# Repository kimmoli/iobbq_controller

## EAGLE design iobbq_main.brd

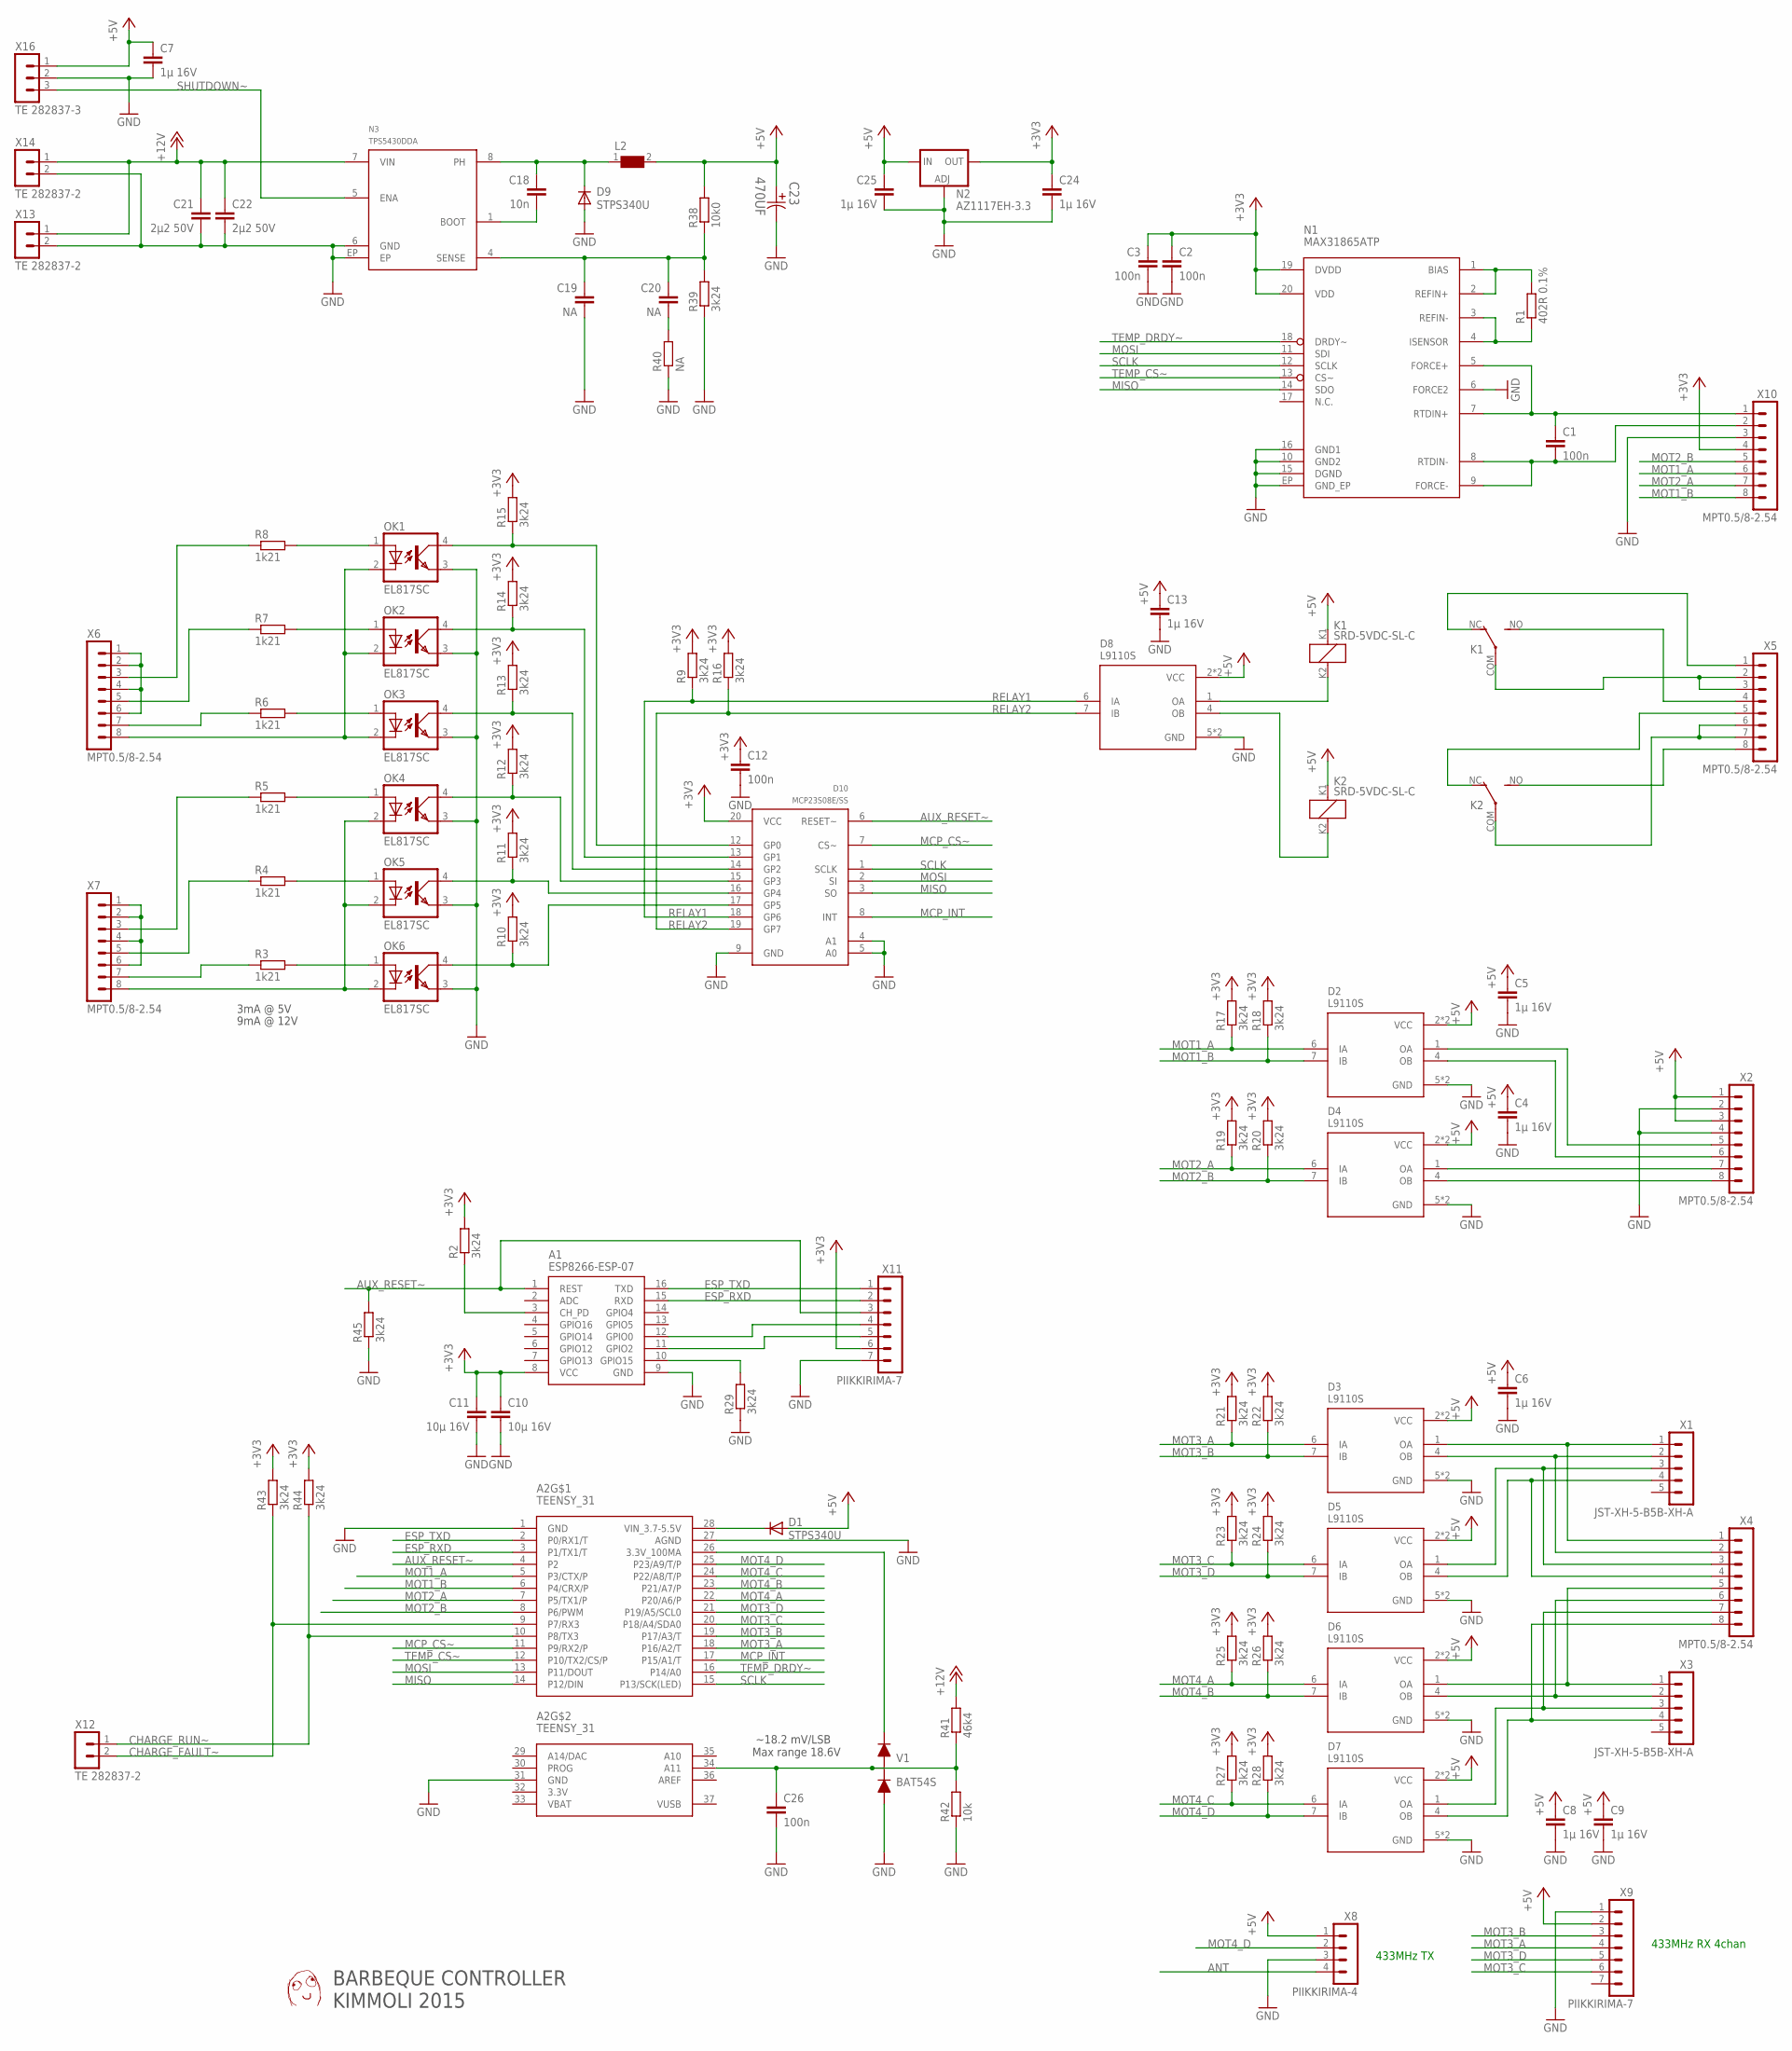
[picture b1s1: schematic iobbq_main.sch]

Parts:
A1: ESP8266-ESP-07
A2: TEENSY_31; TEENSY_31_THONLY
C1, C2, C3, C12, C26: 100n; C0603
C4, C5, C6, C7, C8, C9, C13, C24, C25: 1µ 16V; C0805
C10, C11: 10µ 16V; C0805
C18: 10n; C0805
C19, C20: NA; C0603
C21, C22: 2µ2 50V; C0805
C23: 470UF; CAPAE1350X1400N
D1, D9: STPS340U; SMB
D2, D3, D4, D5, D6, D7, D8: L9110S; SOIC8-N_MC
D10: MCP23S08E/SS; SSOP-20
K1, K2: SRD-5VDC-SL-C; SRD-SL-C
L2: WE-PD-7447709220_1260/1245/1280/1210; WE-PD_1260/1245/1280/1210
N1: MAX31865ATP; TQFN-20
N2: AZ1117EH-3.3; SOT223
N3: TPS5430DDA; SOIC8-N-EP
OK1, OK2, OK3, OK4, OK5, OK6: EL817SC; SMD4-7
R1: 402R 0.1%; R0603
R2, R9, R10, R11, R12, R13, R14, R15, R16, R17, R18, R19, R20, R21, R22, R23, R24, R25, R26, R27, R28, R29, R39, R43, R44, R45: 3k24; R0603
R3, R4, R5, R6, R7, R8: 1k21; R0805
R38: 10k0; R0603
R40: NA; R0603
R41: 46k4; R0603
R42: 10k; R0603
U$3: DAFUG
V1: BAT54S; SOT23
X1, X3: JST-XH-5-B5B-XH-A; JST-XH-5
X2, X4, X5, X6, X7, X10: MPT0.5/8-2.54
X8: PIIKKIRIMA-4
X9, X11: PIIKKIRIMA-7
X12, X13, X14: TE 282837-2; TE_RUUVILIITIN2
X16: TE 282837-3; TE_RUUVILIITIN3

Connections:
+3V3: A1.8 (VCC), C2.1, C3.1, C10.1, C11.1, C12.1, C24.1, D10.20 (VCC), N1.19 (DVDD), N1.20 (VDD), N2.4 (OUT), R2.2, R9.2, R10.2, R11.2, R12.2, R13.2, R14.2, R15.2, R16.2, R17.2, R18.2, R19.2, R20.2, R21.2, R22.2, R23.2, R24.2, R25.2, R26.2, R27.2, R28.2, R43.2, R44.2, X10.4, X11.6
+5V: C4.1, C5.1, C6.1, C7.1, C8.1, C9.1, C13.1, C23.1, C25.1, D1.A, D2.2 (VCC), D2.3 (VCC), D3.2 (VCC), D3.3 (VCC), D4.2 (VCC), D4.3 (VCC), D5.2 (VCC), D5.3 (VCC), D6.2 (VCC), D6.3 (VCC), D7.2 (VCC), D7.3 (VCC), D8.2 (VCC), D8.3 (VCC), K1.K1 (1), K2.K1 (1), L2.2, N2.3 (IN), R38.2, X2.1, X2.3, X8.1, X9.2, X16.1
+12V: C21.1, C22.1, N3.7 (VIN), R41.2, X13.1, X14.1
ANT: X8.4
AUX_RESET~: A1.1 (REST), A2.4 (P2), D10.6 (RESET~), R45.2, X11.3
CHARGE_FAULT~: A2.9 (P7/RX3), R43.1, X12.2
CHARGE_RUN~: A2.10 (P8/TX3), R44.1, X12.1
ESP_RXD: A1.15 (RXD), A2.3 (P1/TX1/T), X11.2
ESP_TXD: A1.16 (TXD), A2.2 (P0/RX1/T), X11.1
GND: A1.9 (GND), A2.1 (GND), A2.27 (AGND), A2.31 (GND), C2.2, C3.2, C4.2, C5.2, C6.2, C7.2, C8.2, C9.2, C10.2, C11.2, C12.2, C13.2, C19.2, C21.2, C22.2, C23.2, C24.2, C25.2, C26.2, D2.5 (GND), D2.8 (GND), D3.5 (GND), D3.8 (GND), D4.5 (GND), D4.8 (GND), D5.5 (GND), D5.8 (GND), D6.5 (GND), D6.8 (GND), D7.5 (GND), D7.8 (GND), D8.5 (GND), D8.8 (GND), D9.A, D10.4 (A1), D10.5 (A0), D10.9 (GND), N1.6 (FORCE2), N1.10 (GND2), N1.15 (DGND), N1.16 (GND1), N1.EP (GND_EP), N2.1 (ADJ), N3.6 (GND), N3.EP, OK1.3 (EMIT), OK2.3 (EMIT), OK3.3 (EMIT), OK4.3 (EMIT), OK5.3 (EMIT), OK6.3 (EMIT), R29.1, R39.1, R40.1, R42.1, R45.1, V1.1, X2.2, X2.4, X8.3, X9.1, X10.3, X11.7, X13.2, X14.2, X16.2
MCP_CS~: A2.11 (P9/RX2/P), D10.7 (CS~)
MCP_INT: A2.17 (P15/A1/T), D10.8 (INT)
MISO: A2.14 (P12/DIN), D10.3 (SO), N1.14 (SDO)
MOSI: A2.13 (P11/DOUT), D10.2 (SI), N1.11 (SDI)
MOT1_A: A2.5 (P3/CTX/P), D2.6 (IA), R17.1, X10.6
MOT1_B: A2.6 (P4/CRX/P), D2.7 (IB), R18.1, X10.8
MOT2_A: A2.7 (P5/TX1/P), D4.6 (IA), R19.1, X10.7
MOT2_B: A2.8 (P6/PWM), D4.7 (IB), R20.1, X10.5
MOT3_A: A2.18 (P16/A2/T), D3.6 (IA), R21.1, X9.4
MOT3_B: A2.19 (P17/A3/T), D3.7 (IB), R22.1, X9.3
MOT3_C: A2.20 (P18/A4/SDA0), D5.6 (IA), R23.1, X9.6
MOT3_D: A2.21 (P19/A5/SCL0), D5.7 (IB), R24.1, X9.5
MOT4_A: A2.22 (P20/A6/P), D6.6 (IA), R25.1
MOT4_B: A2.23 (P21/A7/P), D6.7 (IB), R26.1
MOT4_C: A2.24 (P22/A8/T/P), D7.6 (IA), R27.1
MOT4_D: A2.25 (P23/A9/T/P), D7.7 (IB), R28.1, X8.2
unnamed: OK1.2 (C), OK2.2 (C), OK3.2 (C), X6.8
unnamed: C1.2, N1.8 (RTDIN-), N1.9 (FORCE-), X10.2
unnamed: D3.1 (OA), X1.1, X4.1
unnamed: D3.4 (OB), X1.2, X4.2
unnamed: D5.1 (OA), X1.3, X4.3
unnamed: D5.4 (OB), X1.4, X4.4
unnamed: D6.1 (OA), X3.1, X4.5
unnamed: R6.1, X6.7
unnamed: D4.4 (OB), X2.8
unnamed: D6.4 (OB), X3.2, X4.6
unnamed: D4.1 (OA), X2.7
unnamed: D2.4 (OB), X2.6
unnamed: D2.1 (OA), X2.5
unnamed: D7.1 (OA), X3.3, X4.7
unnamed: D7.4 (OB), X3.4, X4.8
unnamed: D8.4 (OB), K2.K2 (2)
unnamed: A1.10 (GPIO15), R29.2
unnamed: D8.1 (OA), K1.K2 (2)
unnamed: OK4.2 (C), OK5.2 (C), OK6.2 (C), X7.8
unnamed: A1.3 (CH_PD), R2.1
unnamed: D10.17 (GP5), OK6.4 (COL), R10.1
unnamed: D10.16 (GP4), OK5.4 (COL), R11.1
unnamed: C1.1, N1.5 (FORCE+), N1.7 (RTDIN+), X10.1
unnamed: D10.15 (GP3), OK4.4 (COL), R12.1
unnamed: N1.3 (REFIN-), N1.4 (ISENSOR), R1.1
unnamed: N1.1 (BIAS), N1.2 (REFIN+), R1.2
unnamed: D10.14 (GP2), OK3.4 (COL), R13.1
unnamed: D10.13 (GP1), OK2.4 (COL), R14.1
unnamed: D10.12 (GP0), OK1.4 (COL), R15.1
unnamed: R7.1, X6.5
unnamed: OK1.1 (A), R8.2
unnamed: OK2.1 (A), R7.2
unnamed: OK3.1 (A), R6.2
unnamed: OK4.1 (A), R5.2
unnamed: OK5.1 (A), R4.2
unnamed: OK6.1 (A), R3.2
unnamed: R8.1, X6.3
unnamed: C18.1, D9.C, L2.1, N3.8 (PH)
unnamed: R3.1, X7.7
unnamed: R4.1, X7.5
unnamed: X6.1, X6.2, X6.4, X6.6
unnamed: R5.1, X7.3
unnamed: X7.1, X7.2, X7.4, X7.6
unnamed: A2.28 (VIN_3.7-5.5V), D1.C
unnamed: A1.12 (GPIO0), X11.4
unnamed: A1.11 (GPIO2), X11.5
unnamed: C18.2, N3.1 (BOOT)
unnamed: C19.1, C20.1, N3.4 (SENSE), R38.1, R39.2
unnamed: C20.2, R40.2
unnamed: A2.34 (A11), C26.1, R41.1, R42.2, V1.3
unnamed: A2.26 (3.3V_100MA), V1.2
RELAY1: D8.6 (IA), D10.18 (GP6), R9.1
RELAY2: D8.7 (IB), D10.19 (GP7), R16.1
RLY1COM: K1.COM, X5.2, X5.3
RLY1NC: K1.NC (O), X5.1
RLY1NO: K1.NO (S), X5.4
RLY2COM: K2.COM, X5.6, X5.7
RLY2NC: K2.NC (O), X5.5
RLY2NO: K2.NO (S), X5.8
SCLK: A2.15 (P13/SCK(LED)), D10.1 (SCLK), N1.12 (SCLK)
SHUTDOWN~: N3.5 (ENA), X16.3
TEMP_CS~: A2.12 (P10/TX2/CS/P), N1.13 (CS~)
TEMP_DRDY~: A2.16 (P14/A0), N1.18 (DRDY~)

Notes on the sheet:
433MHz TX
433MHz RX 4chan
~18.2 mV/LSB Max range 18.6V
3mA @ 5V
9mA @ 12V
BARBEQUE CONTROLLER KIMMOLI 2015

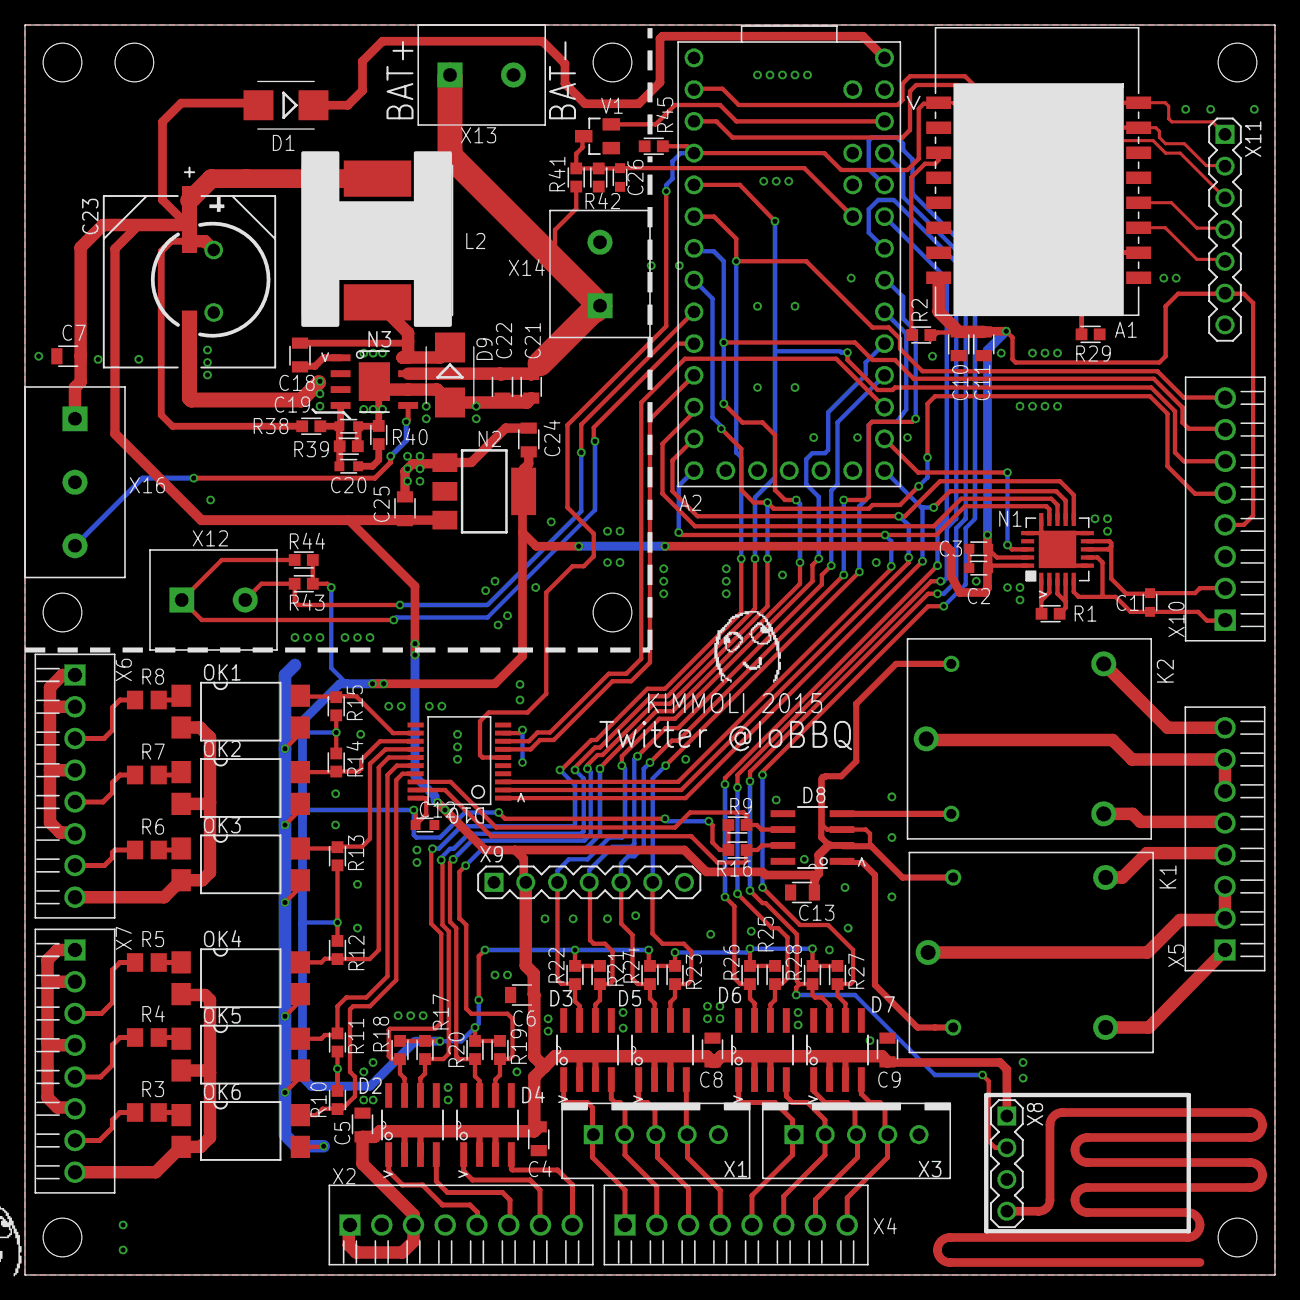
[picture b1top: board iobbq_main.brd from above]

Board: 2 copper layers, 100.0 x 100.0 mm, 102 parts (1 on the bottom side), 88 nets.

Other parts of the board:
U$1, U$2: DAFUG

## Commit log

2015-04-05 update values
2015-04-05 pull ESP8266 GPIO15 down
